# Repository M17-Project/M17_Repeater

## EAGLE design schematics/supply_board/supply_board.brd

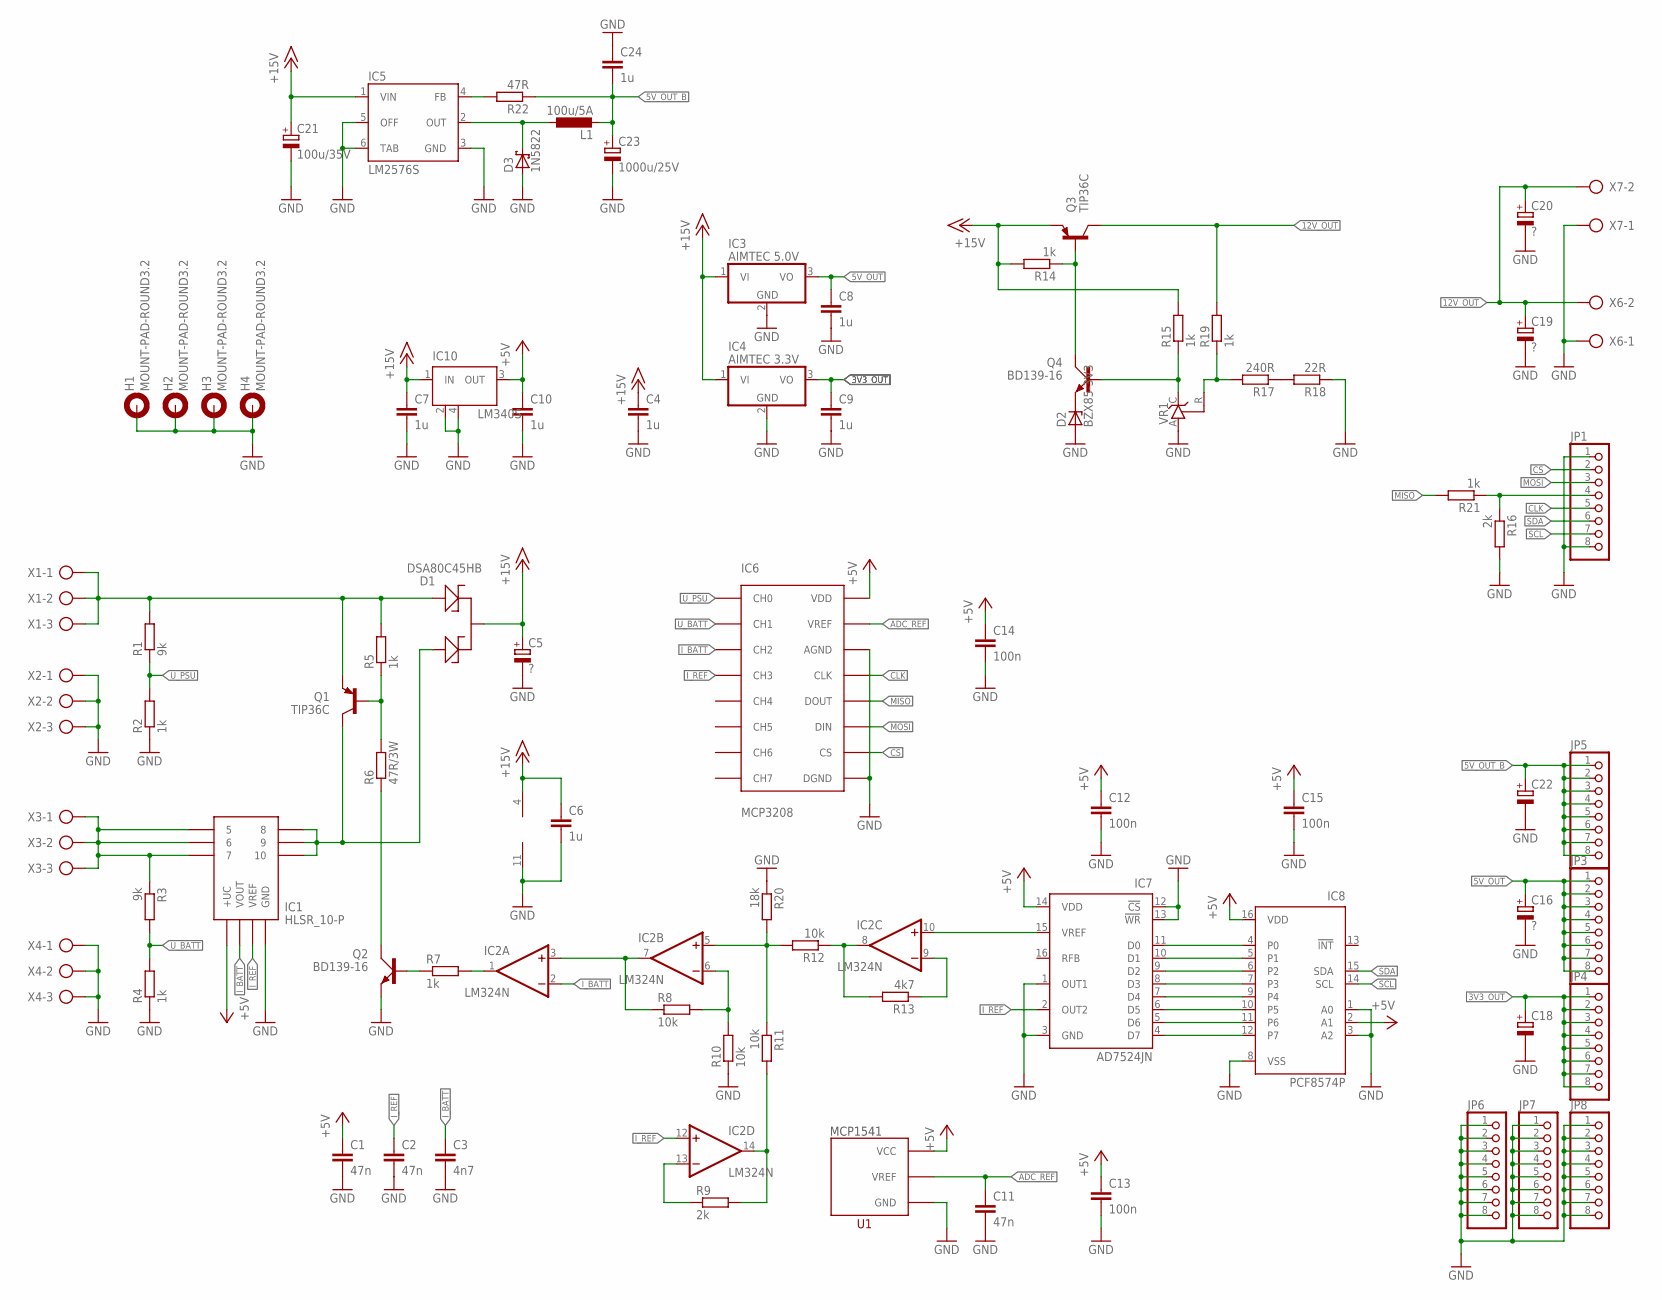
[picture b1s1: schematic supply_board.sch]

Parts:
C1, C2, C11: 47n; C0805
C3: 4n7; C0805
C4, C6, C7, C8, C9, C10, C24: 1u; C0805
C5, C19, C20: ?; E5-13
C12, C13, C14, C15: 100n; C0805
C16: ?; E2,5-6
C18, C22: CPOL-EUE2.5-6; E2,5-6
C21: 100u/35V; E5-10,5
C23: 1000u/25V; E5-10,5
D1: DSA80C45HB; TO247BV
D2: BZX85-3V3; DO41Z10
D3: 1N5822; C4111-15
H1, H2, H3, H4: MOUNT-PAD-ROUND3.2; 3,2-PAD
IC1: HLSR_10-P; HLSR16-P
IC2: LM324N; DIL14
IC3: AIMTEC 5.0V; TO220V
IC4: AIMTEC 3.3V; TO220V
IC5: LM2576S; TO263-5
IC6: MCP3208; DIL16
IC7: AD7524JN; DIL16
IC8: PCF8574P; DIL16
IC10: LM340S; SOT223
JP1, JP3, JP4, JP5, JP6, JP7, JP8: PINHD-1X8; 1X08
L1: 100u/5A; TJ5-U2
Q1, Q3: TIP36C; TO247-V
Q2, Q4: BD139-16; TO126AV
R1, R3: 9k; R0805
R2, R4, R5, R7, R14, R15, R19, R21: 1k; R0805
R6: 47R/3W; 0617/22
R8, R10, R11, R12: 10k; R0805
R9, R16: 2k; R0805
R13: 4k7; R0805
R17: 240R; R0805
R18: 22R; R0805
R20: 18k; R0805
R22: 47R; R0805
U1: VOLT_REFERENCE; SOT23
VR1: TL431CLP; TO92-CLP
X1, X2, X3, X4: AK500/3
X6, X7: AK500/2

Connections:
3V3_OUT: C9.1, C18.+, IC4.3 (VO), JP4.1, JP4.2, JP4.3, JP4.4, JP4.5, JP4.6, JP4.7, JP4.8
5V_OUT: C8.1, C16.+, IC3.3 (VO), JP3.1, JP3.2, JP3.3, JP3.4, JP3.5, JP3.6, JP3.7, JP3.8
5V_OUT_B: C22.+, C23.+, C24.2, JP5.1, JP5.2, JP5.3, JP5.4, JP5.5, JP5.6, JP5.7, JP5.8, L1.2, R22.1
12V_OUT: C19.+, C20.+, Q3.2 (C), R19.2, X6.2, X7.2
+5V: C1.1, C10.1, C12.1, C13.1, C14.1, C15.1, IC1.4 (+UC), IC6.VDD, IC7.14 (VDD), IC8.2 (A1), IC8.16 (VDD), IC10.3 (OUT), U1.1 (VCC)
+15V: C4.1, C5.+, C6.1, C7.1, C21.+, D1.2, IC2.4 (V+), IC3.1 (VI), IC4.1 (VI), IC5.1 (VIN), IC10.1 (IN), Q3.3 (E), R14.2, R15.2
ADC_REF: C11.1, IC6.VREF, U1.2 (VREF)
CLK: IC6.CLK, JP1.5
CS: IC6.CS, JP1.2
GND: C1.2, C2.2, C3.2, C4.2, C5.-, C6.2, C7.2, C8.2, C9.2, C10.2, C11.2, C12.2, C13.2, C14.2, C15.2, C16.-, C18.-, C19.-, C20.-, C21.-, C22.-, C23.-, C24.1, D2.A, D3.A, H1.B3,2, H2.B3,2, H3.B3,2, H4.B3,2, IC1.3 (GND), IC2.11 (V-), IC3.2 (GND), IC4.2 (GND), IC5.3 (GND), IC5.5 (OFF), IC5.6 (TAB), IC6.AGND, IC6.DGND, IC7.1 (OUT1), IC7.3 (GND), IC7.12 (!CS), IC7.13 (!WR), IC8.1 (A0), IC8.3 (A2), IC8.8 (VSS), IC10.2 (GND), IC10.4 (GND), JP1.1, JP1.8, JP6.1, JP6.2, JP6.3, JP6.4, JP6.5, JP6.6, JP6.7, JP6.8, JP7.1, JP7.2, JP7.3, JP7.4, JP7.5, JP7.6, JP7.7, JP7.8, JP8.1, JP8.2, JP8.3, JP8.4, JP8.5, JP8.6, JP8.7, JP8.8, Q2.E, R2.1, R4.1, R10.1, R16.2, R18.1, R20.1, U1.3 (GND), VR1.A, X2.1, X2.2, X2.3, X4.1, X4.2, X4.3, X6.1, X7.1
I_BATT: C3.1, IC1.2 (VOUT), IC2.2 (-IN), IC6.CH2
I_REF: C2.1, IC1.1 (VREF), IC2.12 (+IN), IC6.CH3, IC7.2 (OUT2)
MISO: IC6.DOUT, R21.2
MOSI: IC6.DIN, JP1.3
unnamed: IC1.5, IC1.6, IC1.7, R3.1, X3.1, X3.2, X3.3
unnamed: D1.3, IC1.8, IC1.9, IC1.10, Q1.2 (C)
unnamed: Q1.1 (B), R5.1, R6.2
unnamed: Q2.C, R6.1
unnamed: IC2.6 (-IN), R8.2, R10.2
unnamed: D1.1, Q1.3 (E), R1.2, R5.2, X1.1, X1.2, X1.3
unnamed: Q2.B, R7.1
unnamed: IC2.1 (OUT), R7.2
unnamed: IC2.13 (-IN), R9.1
unnamed: IC2.3 (+IN), IC2.7 (OUT), R8.1
unnamed: IC2.14 (OUT), R9.2, R11.2
unnamed: IC2.5 (+IN), R11.1, R12.2, R20.2
unnamed: IC2.8 (OUT), R12.1, R13.2
unnamed: IC7.11 (D0), IC8.4 (P0)
unnamed: IC7.10 (D1), IC8.5 (P1)
unnamed: IC7.9 (D2), IC8.6 (P2)
unnamed: IC7.8 (D3), IC8.7 (P3)
unnamed: Q3.1 (B), Q4.C, R14.1
unnamed: IC7.7 (D4), IC8.9 (P4)
unnamed: IC7.6 (D5), IC8.10 (P5)
unnamed: IC7.5 (D6), IC8.11 (P6)
unnamed: IC7.4 (D7), IC8.12 (P7)
unnamed: Q4.B, R15.1, VR1.C
unnamed: D2.C, Q4.E
unnamed: IC2.9 (-IN), R13.1
unnamed: IC2.10 (+IN), IC7.15 (VREF)
unnamed: JP1.4, R16.1, R21.1
unnamed: R17.1, R18.2
unnamed: IC5.4 (FB), R22.2
unnamed: R17.2, R19.1, VR1.R
unnamed: D3.C, IC5.2 (OUT), L1.1
SCL: IC8.14 (SCL), JP1.7
SDA: IC8.15 (SDA), JP1.6
U_BATT: IC6.CH1, R3.2, R4.2
U_PSU: IC6.CH0, R1.1, R2.2

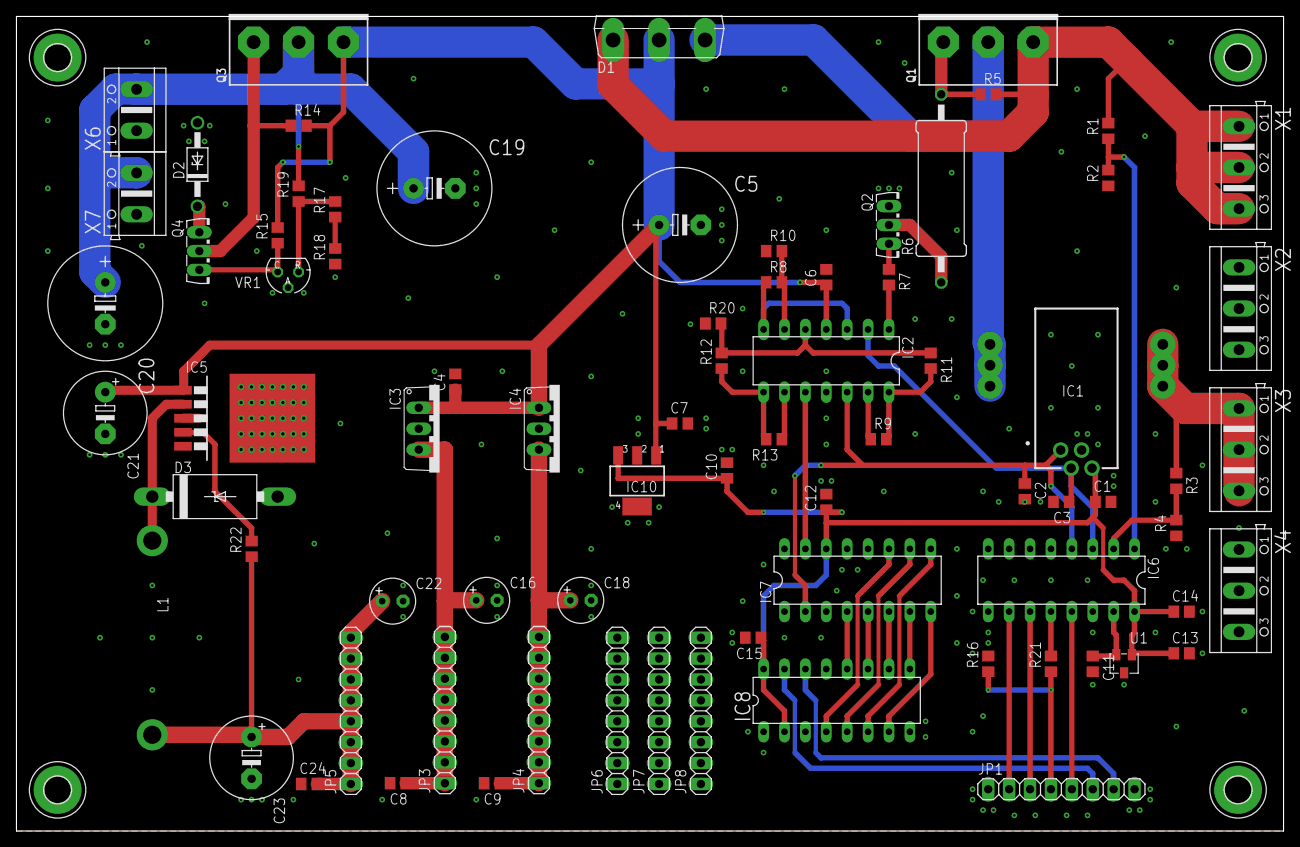
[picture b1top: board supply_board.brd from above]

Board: 2 copper layers, 154.0 x 99.0 mm, 81 parts (0 on the bottom side), 49 nets.

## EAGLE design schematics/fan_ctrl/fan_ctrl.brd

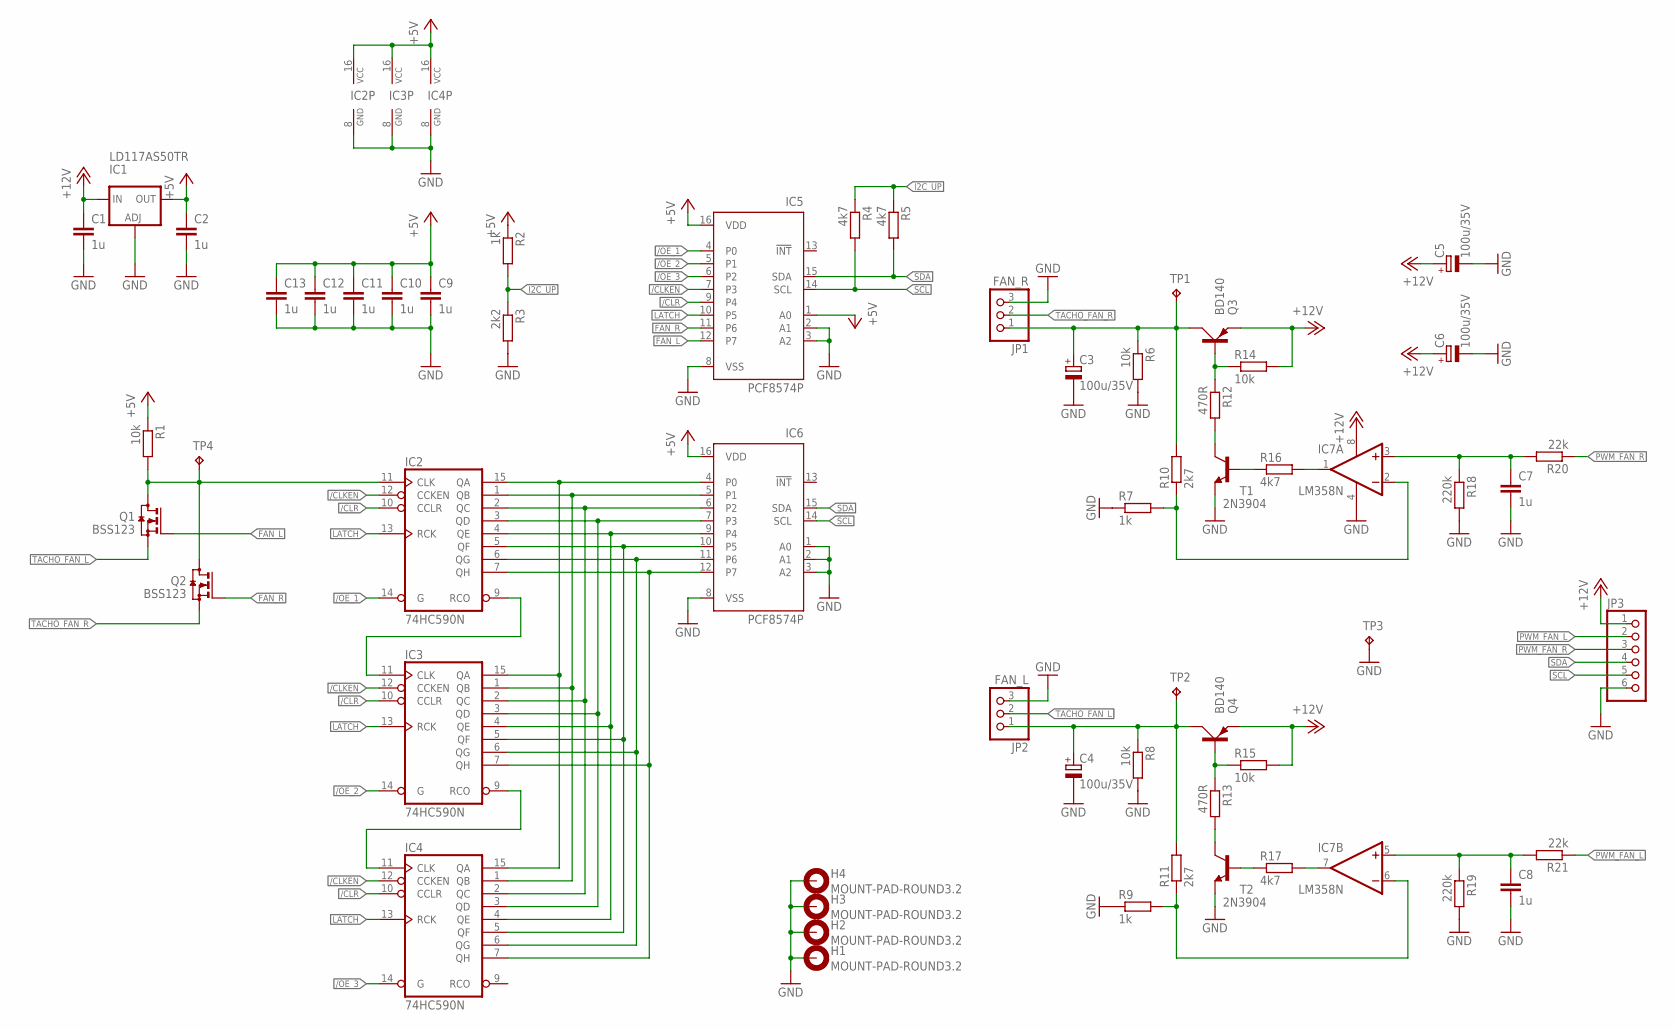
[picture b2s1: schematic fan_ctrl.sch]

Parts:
C1, C2, C7, C8, C9, C10, C11, C12, C13: 1u; C0805
C3, C4, C5, C6: 100u/35V; E3,5-8
H1, H2, H3, H4: MOUNT-PAD-ROUND3.2; 3,2-PAD
IC1: LD117AS50TR; SOT223
IC2, IC3, IC4: 74HC590N; DIL16
IC5, IC6: PCF8574P; DIL16
IC7: LM358N; DIL08
JP1: FAN_R; 1X03
JP2: FAN_L; 1X03
JP3: PINHD-1X6; 1X06
Q1, Q2: BSS123; SOT23
Q3, Q4: BD140; TO126AV
R1, R6, R8, R14, R15: 10k; R0805
R2, R7, R9: 1k; R0805
R3: 2k2; R0805
R4, R5, R16, R17: 4k7; R0805
R10, R11: 2k7; R0805
R12, R13: 470R; R0805
R18, R19: 220k; R0805
R20, R21: 22k; R0805
T1, T2: 2N3904; TO92-EBC
TP1, TP2, TP3, TP4: TPB2,54; B2,54

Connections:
+5V: C2.1, C9.1, C10.1, C11.1, C12.1, C13.1, IC1.4 (OUT), IC2.16 (VCC), IC3.16 (VCC), IC4.16 (VCC), IC5.1 (A0), IC5.16 (VDD), IC6.16 (VDD), R1.1, R2.1
+12V: C1.1, C5.+, C6.+, IC1.3 (IN), IC7.8 (V+), JP3.1, Q3.E, Q4.E, R14.2, R15.2
/CLKEN: IC2.12 (CCKEN), IC3.12 (CCKEN), IC4.12 (CCKEN), IC5.7 (P3)
/CLR: IC2.10 (CCLR), IC3.10 (CCLR), IC4.10 (CCLR), IC5.9 (P4)
/OE_1: IC2.14 (G), IC5.4 (P0)
/OE_2: IC3.14 (G), IC5.5 (P1)
/OE_3: IC4.14 (G), IC5.6 (P2)
FAN_L: IC5.12 (P7), Q1.1 (G)
FAN_R: IC5.11 (P6), Q2.1 (G)
GND: C1.2, C2.2, C3.-, C4.-, C5.-, C6.-, C7.2, C8.2, C9.2, C10.2, C11.2, C12.2, C13.2, H1.B3,2, H2.B3,2, H3.B3,2, H4.B3,2, IC1.1 (ADJ), IC2.8 (GND), IC3.8 (GND), IC4.8 (GND), IC5.2 (A1), IC5.3 (A2), IC5.8 (VSS), IC6.1 (A0), IC6.2 (A1), IC6.3 (A2), IC6.8 (VSS), IC7.4 (V-), JP1.3, JP2.3, JP3.6, R3.2, R6.2, R7.1, R8.2, R9.1, R18.2, R19.2, T1.E, T2.E, TP3.TP
I2C_UP: R2.2, R3.1, R4.1, R5.1
LATCH: IC2.13 (RCK), IC3.13 (RCK), IC4.13 (RCK), IC5.10 (P5)
unnamed: IC2.15 (QA), IC3.15 (QA), IC4.15 (QA), IC6.4 (P0)
unnamed: IC2.1 (QB), IC3.1 (QB), IC4.1 (QB), IC6.5 (P1)
unnamed: IC2.2 (QC), IC3.2 (QC), IC4.2 (QC), IC6.6 (P2)
unnamed: IC2.3 (QD), IC3.3 (QD), IC4.3 (QD), IC6.7 (P3)
unnamed: IC2.4 (QE), IC3.4 (QE), IC4.4 (QE), IC6.9 (P4)
unnamed: IC2.11 (CLK), Q1.3 (D), Q2.3 (D), R1.2, TP4.TP
unnamed: IC2.6 (QG), IC3.6 (QG), IC4.6 (QG), IC6.11 (P6)
unnamed: C7.1, IC7.3 (+IN), R18.1, R20.2
unnamed: R12.2, T1.C
unnamed: C8.1, IC7.5 (+IN), R19.1, R21.2
unnamed: Q3.B, R12.1, R14.1
unnamed: IC3.9 (RCO), IC4.11 (CLK)
unnamed: R13.2, T2.C
unnamed: C3.+, JP1.1, Q3.C, R6.1, R10.2, TP1.TP
unnamed: IC7.6 (-IN), R9.2, R11.1
unnamed: Q4.B, R13.1, R15.1
unnamed: R16.1, T1.B
unnamed: C4.+, JP2.1, Q4.C, R8.1, R11.2, TP2.TP
unnamed: IC7.2 (-IN), R7.2, R10.1
unnamed: IC7.1 (OUT), R16.2
unnamed: R17.1, T2.B
unnamed: IC7.7 (OUT), R17.2
unnamed: IC2.9 (RCO), IC3.11 (CLK)
unnamed: IC2.5 (QF), IC3.5 (QF), IC4.5 (QF), IC6.10 (P5)
unnamed: IC2.7 (QH), IC3.7 (QH), IC4.7 (QH), IC6.12 (P7)
PWM_FAN_L: JP3.2, R21.1
PWM_FAN_R: JP3.3, R20.1
SCL: IC5.14 (SCL), IC6.14 (SCL), JP3.5, R4.2
SDA: IC5.15 (SDA), IC6.15 (SDA), JP3.4, R5.2
TACHO_FAN_L: JP2.2, Q1.2 (S)
TACHO_FAN_R: JP1.2, Q2.2 (S)

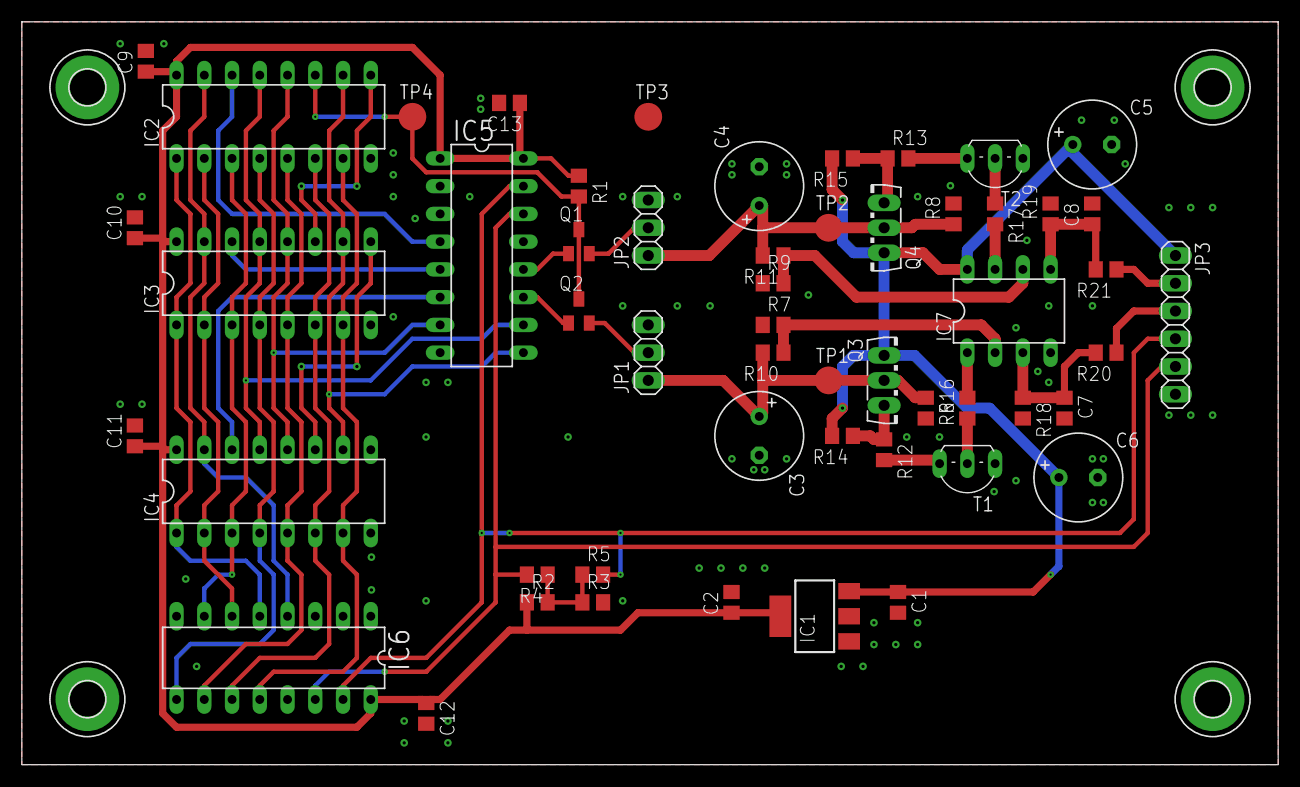
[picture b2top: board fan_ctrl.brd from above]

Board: 2 copper layers, 115.0 x 68.0 mm, 58 parts (0 on the bottom side), 43 nets.

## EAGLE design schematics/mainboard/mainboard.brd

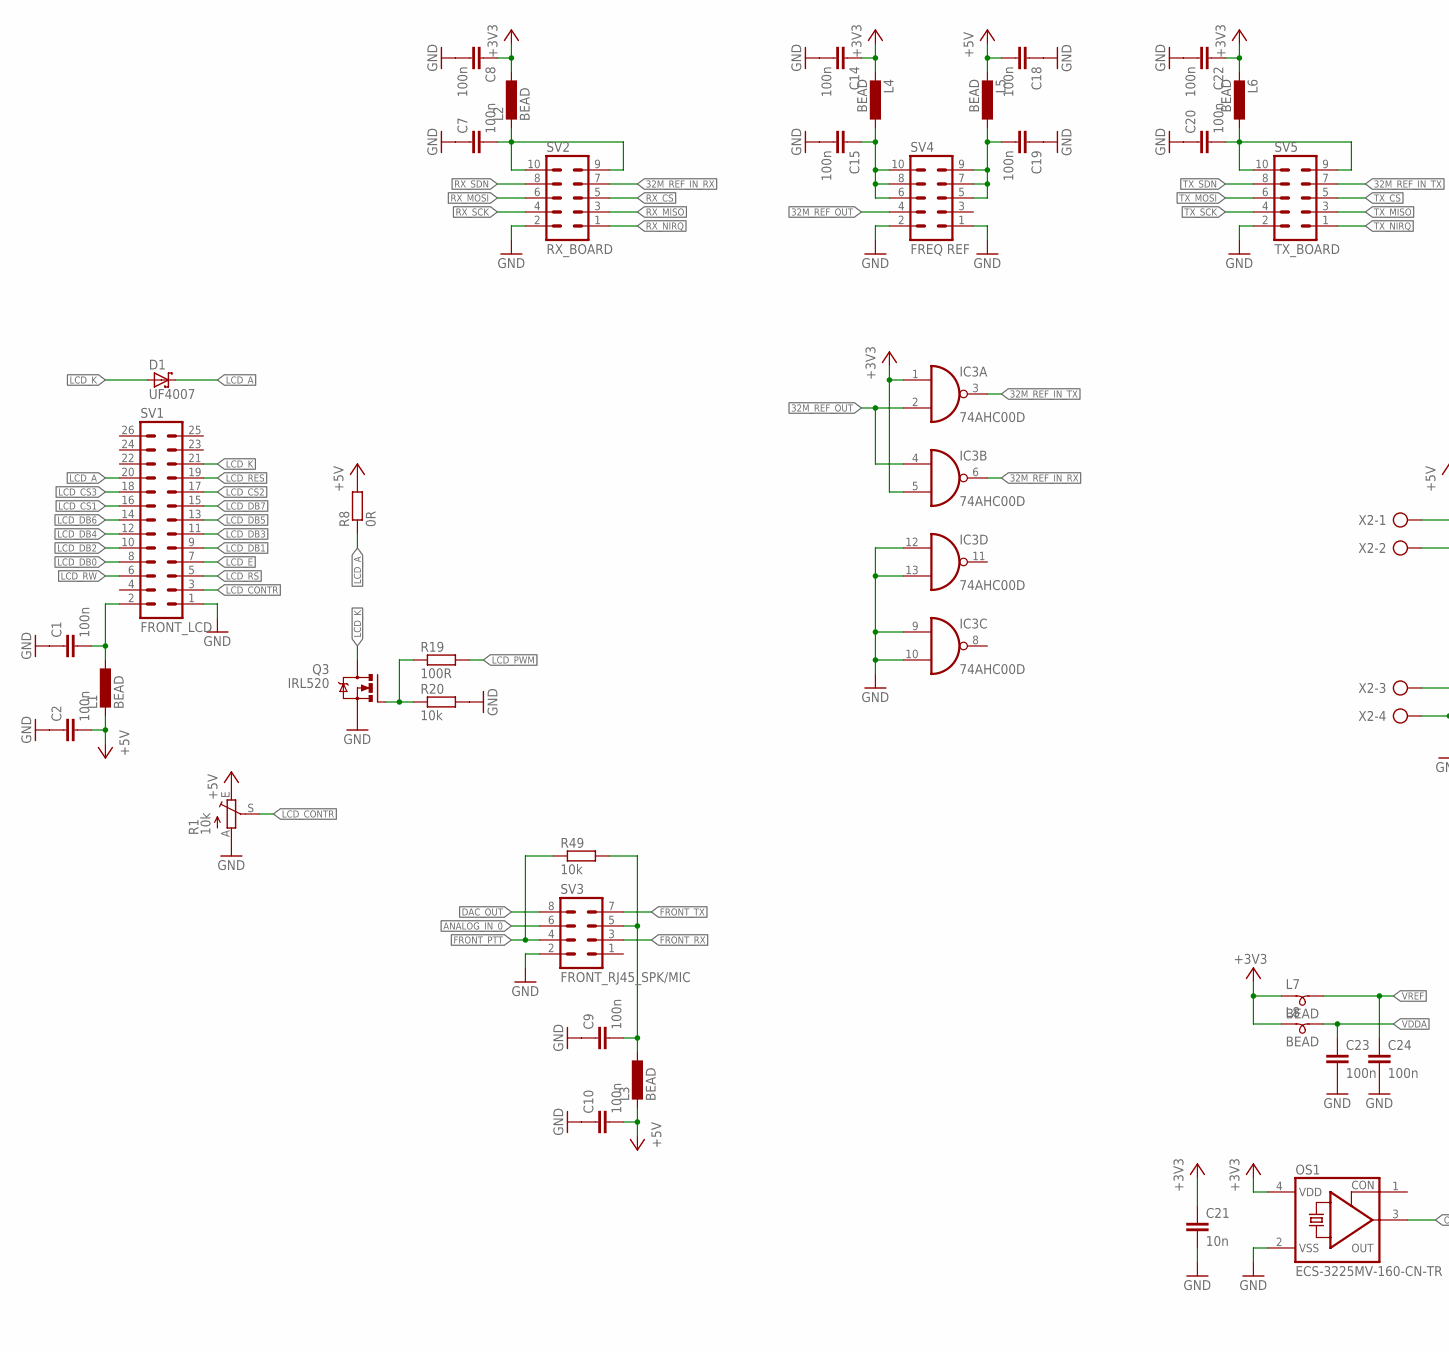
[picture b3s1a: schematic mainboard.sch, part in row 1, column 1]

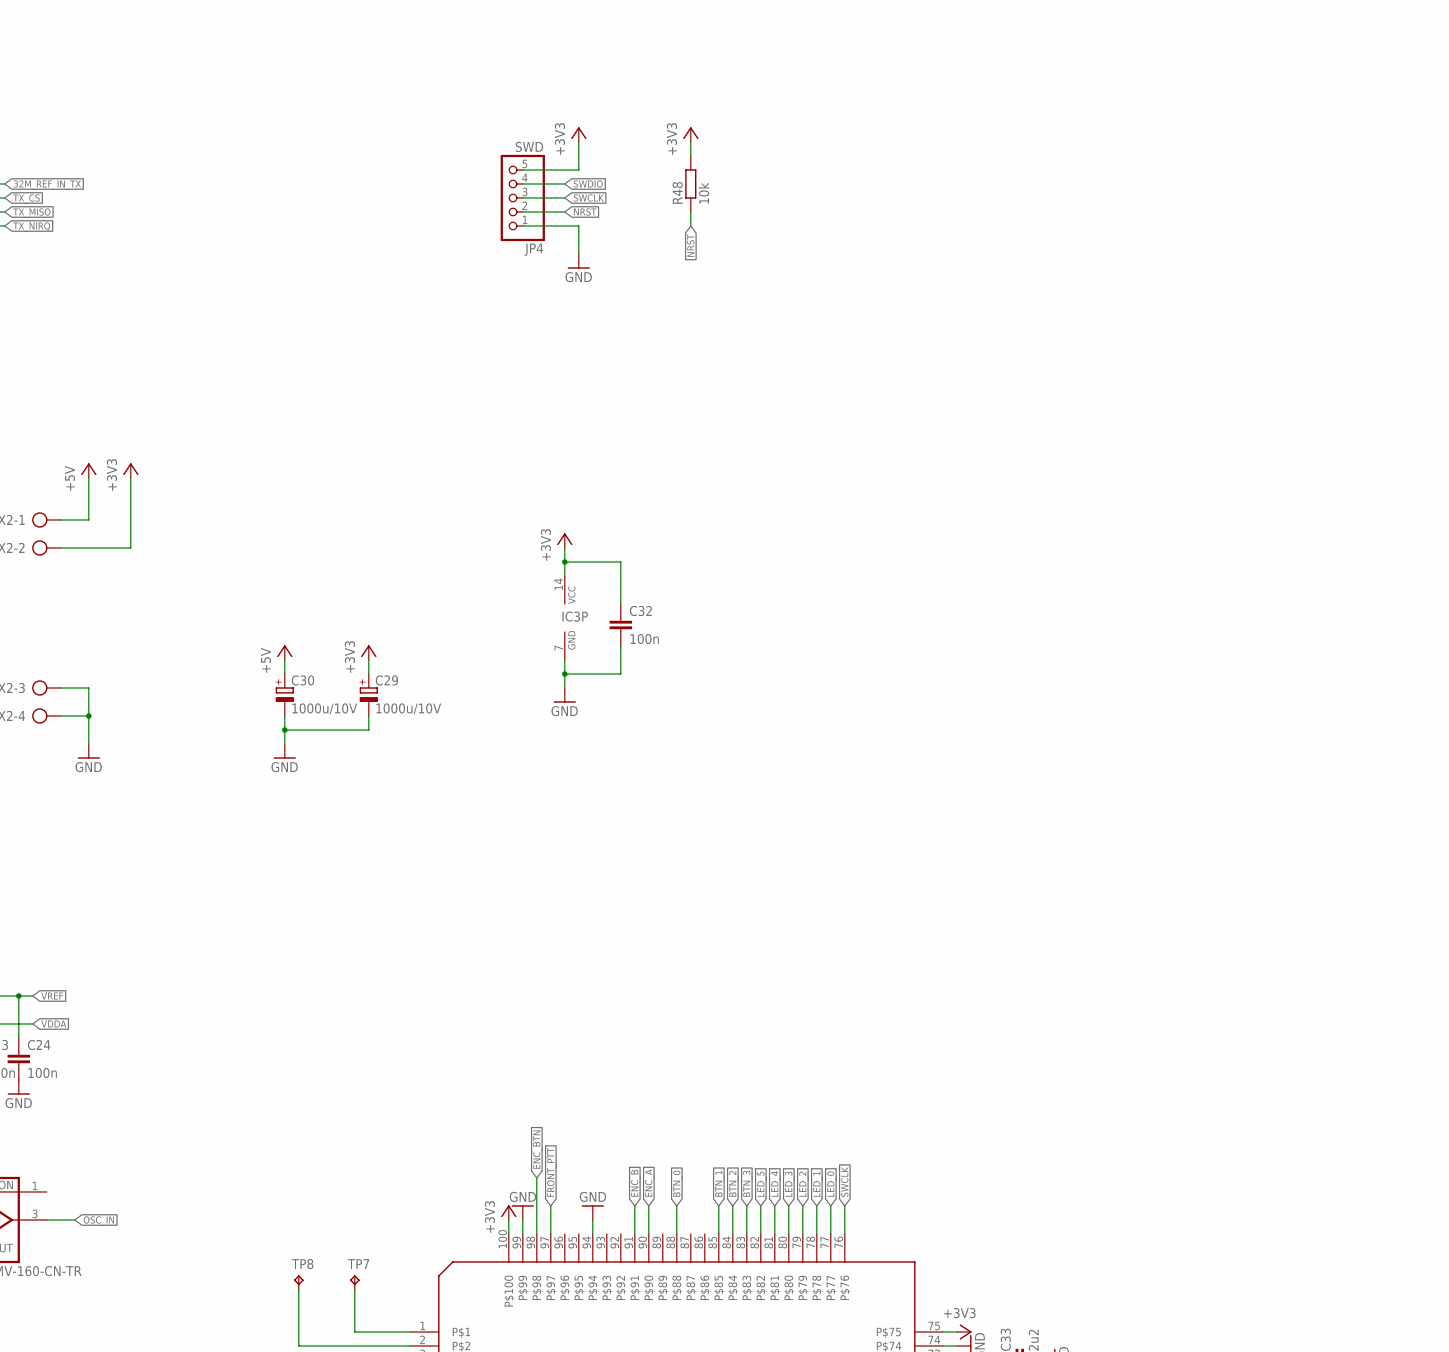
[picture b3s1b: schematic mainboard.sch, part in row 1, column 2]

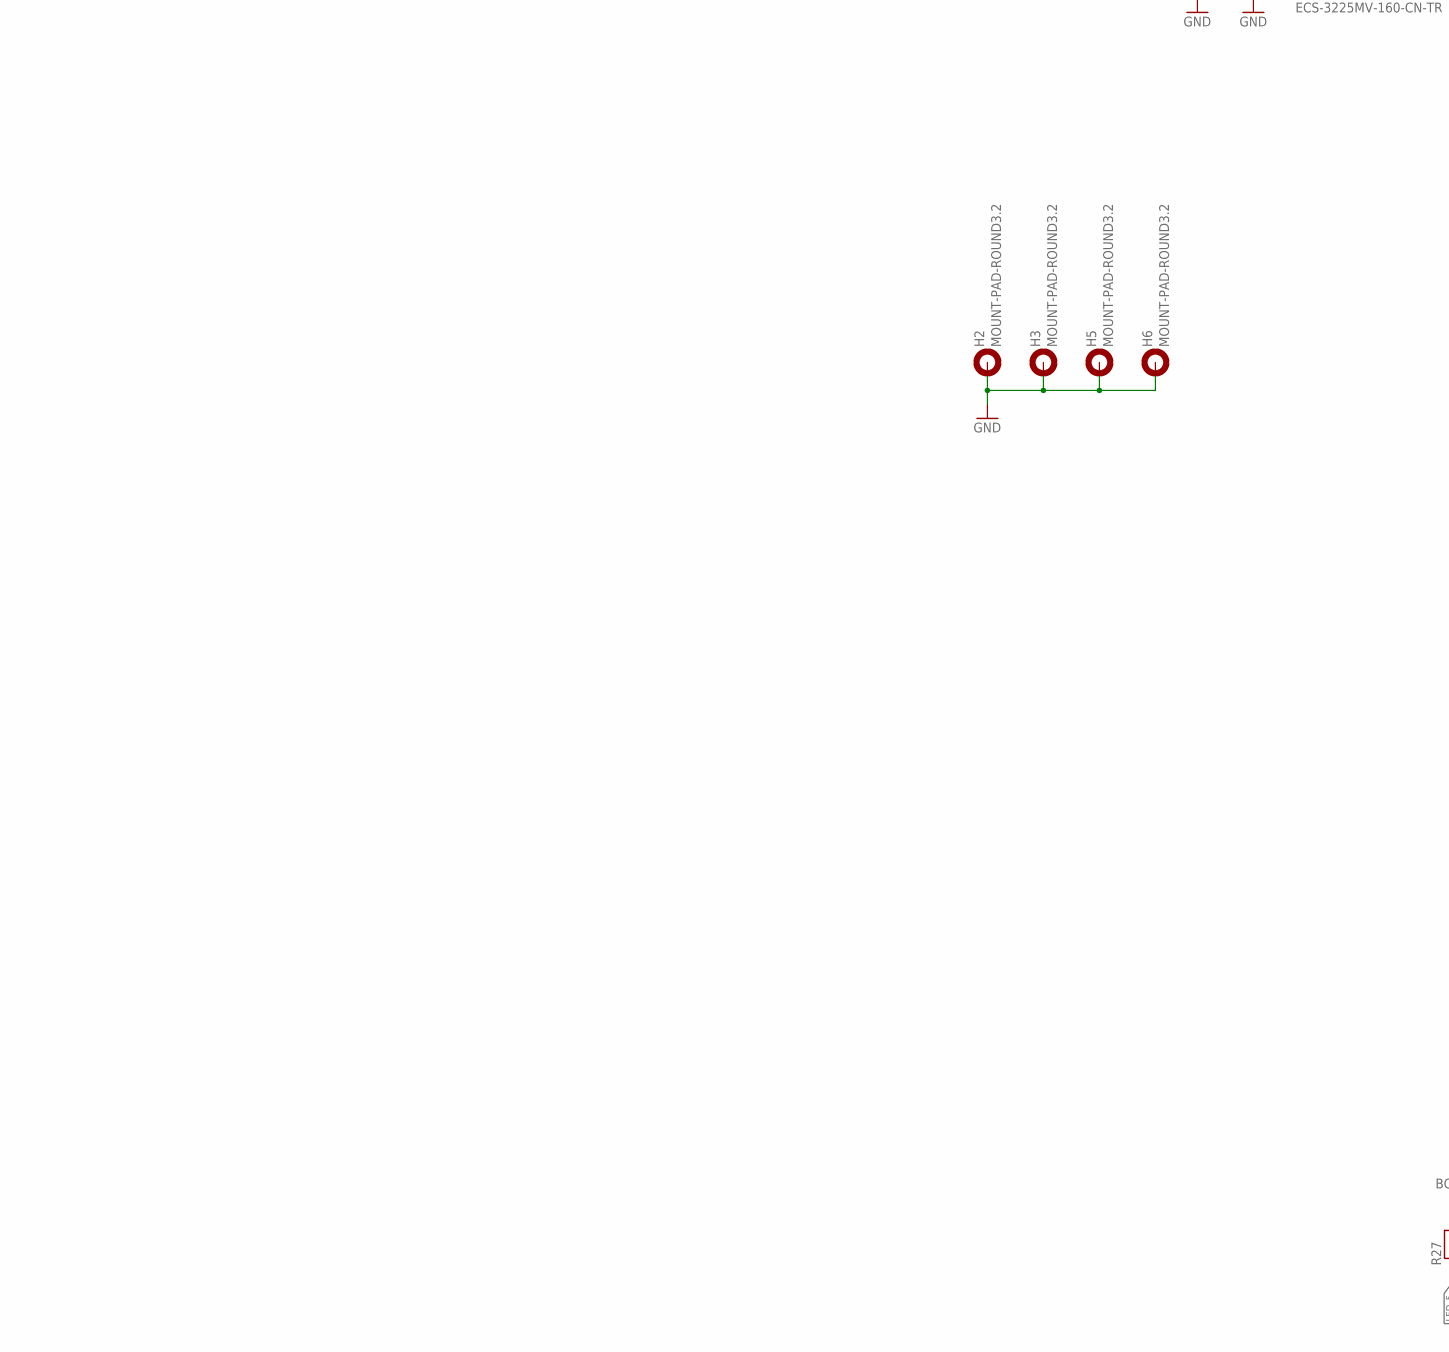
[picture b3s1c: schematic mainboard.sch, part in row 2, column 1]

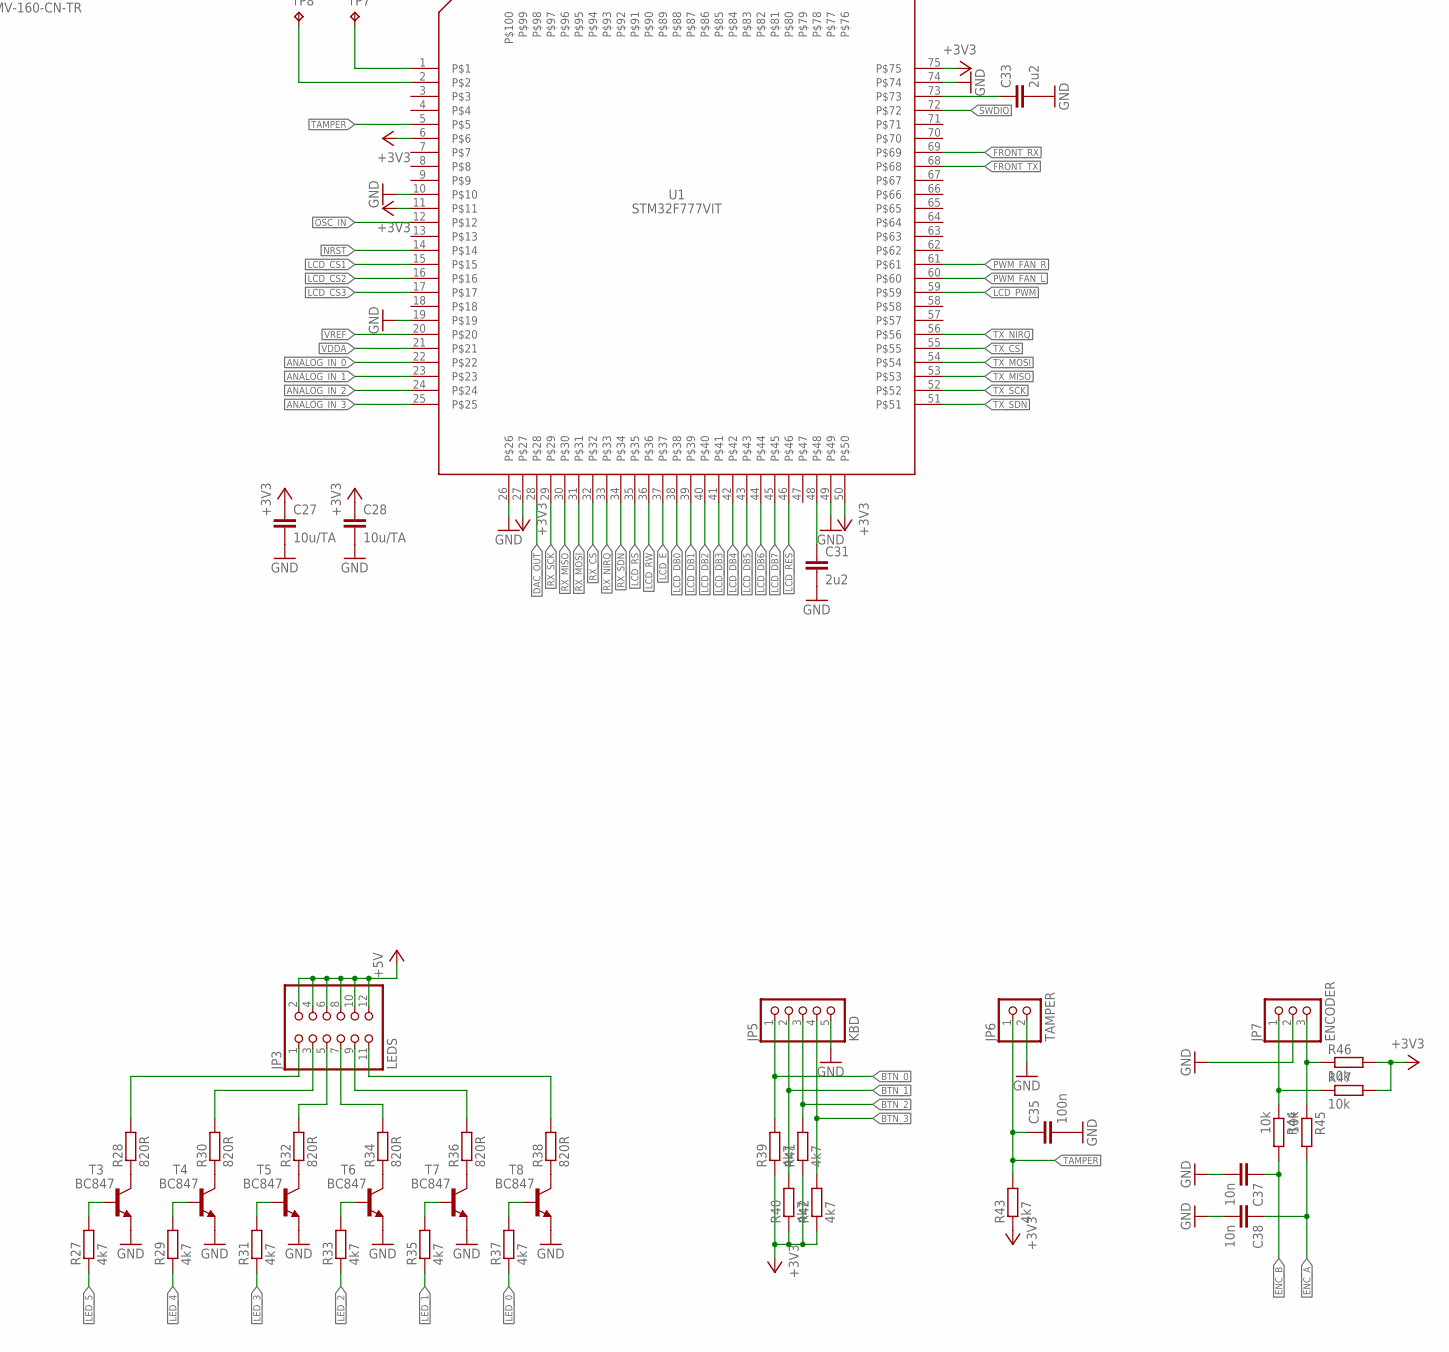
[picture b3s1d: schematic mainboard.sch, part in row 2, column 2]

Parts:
C1, C2, C7, C8, C9, C10, C14, C15, C18, C19, C20, C22, C23, C24, C32, C35: 100n; C0805
C21, C37, C38: 10n; C0805
C27, C28: 10u/TA; C1206
C29, C30: 1000u/10V; E3,5-8
C31, C33: 2u2; C0805
D1: UF4007; DO41-7.6
H2, H3, H5, H6: MOUNT-PAD-ROUND3.2; 3,2-PAD
IC3: 74AHC00D; SO14
JP3: LEDS; 2X06
JP4: SWD; 1X05
JP5: KBD; 1X05
JP6: TAMPER; 1X02
JP7: ENCODER; 1X03
L1, L2, L3, L4, L5, L6: BEAD; 0204/7
L7, L8: BEAD; SM-B5
OS1: ECS-3225MV-160-CN-TR; 3.4X2.7-4-PAD
Q3: IRL520; TO220BV
R1: 10k; CA6V
R8: 0R; R1206
R19: 100R; R0805
R20, R44, R45, R46, R47, R48, R49: 10k; R0805
R27, R29, R31, R33, R35, R37, R39, R40, R41, R42, R43: 4k7; R0805
R28, R30, R32, R34, R36, R38: 820R; R0805
SV1: FRONT_LCD; ML26
SV2: RX_BOARD; ML10
SV3: FRONT_RJ45_SPK/MIC; MA04-2
SV4: FREQ REF; ML10
SV5: TX_BOARD; ML10
T3, T4, T5, T6, T7, T8: BC847; SOT23
TP7, TP8: TPB2,54; B2,54
U1: STM32F777VIT; LQFP100
X2: AK500/4

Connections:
32M_REF_IN_RX: IC3.6 (O), SV2.7
32M_REF_IN_TX: IC3.3 (O), SV5.7
32M_REF_OUT: IC3.2 (I1), IC3.4 (I0), SV4.4
+3V3: C8.1, C14.1, C21.1, C22.1, C27.1, C28.1, C29.+, C32.1, IC3.1 (I0), IC3.5 (I1), IC3.14 (VCC), JP4.5, L2.1, L4.2, L6.2, L7.1, L8.1, OS1.4 (VDD), R39.1, R40.1, R41.1, R42.1, R43.1, R46.2, R47.2, R48.2, U1.6, U1.11, U1.27, U1.50, U1.75, U1.100, X2.2
+5V: C2.2, C10.2, C18.2, C30.+, JP3.2, JP3.4, JP3.6, JP3.8, JP3.10, JP3.12, L1.2, L3.2, L5.2, R1.E, R8.2, X2.1
ANALOG_IN_0: SV3.6, U1.22
ANALOG_IN_1: U1.23
ANALOG_IN_2: U1.24
ANALOG_IN_3: U1.25
BTN_0: JP5.1, R39.2, U1.88
BTN_1: JP5.2, R40.2, U1.85
BTN_2: JP5.3, R41.2, U1.84
BTN_3: JP5.4, R42.2, U1.83
DAC_OUT: SV3.8, U1.28
ENC_A: C38.1, R45.2, U1.90
ENC_B: C37.1, R44.2, U1.91
ENC_BTN: U1.98
FRONT_PTT: R49.1, SV3.4, U1.97
FRONT_RX: SV3.3, U1.69
FRONT_TX: SV3.7, U1.68
GND: C1.1, C2.1, C7.1, C8.2, C9.1, C10.1, C14.2, C15.2, C18.1, C19.1, C20.1, C21.2, C22.2, C23.2, C24.2, C27.2, C28.2, C29.-, C30.-, C31.2, C32.2, C33.2, C35.2, C37.2, C38.2, H2.B3,2, H3.B3,2, H5.B3,2, H6.B3,2, IC3.7 (GND), IC3.9 (I0), IC3.10 (I1), IC3.12 (I0), IC3.13 (I1), JP4.1, JP5.5, JP6.2, JP7.2, OS1.2 (VSS), Q3.S, R1.A, R20.2, SV1.1, SV2.2, SV3.2, SV4.1, SV4.2, SV5.2, T3.2 (E), T4.2 (E), T5.2 (E), T6.2 (E), T7.2 (E), T8.2 (E), U1.10, U1.19, U1.26, U1.49, U1.74, U1.94, U1.99, X2.3, X2.4
LCD_A: D1.C, R8.1, SV1.20
LCD_CONTR: R1.S, SV1.3
LCD_CS1: SV1.16, U1.15
LCD_CS2: SV1.17, U1.16
LCD_CS3: SV1.18, U1.17
LCD_DB0: SV1.8, U1.38
LCD_DB1: SV1.9, U1.39
LCD_DB2: SV1.10, U1.40
LCD_DB3: SV1.11, U1.41
LCD_DB4: SV1.12, U1.42
LCD_DB5: SV1.13, U1.43
LCD_DB6: SV1.14, U1.44
LCD_DB7: SV1.15, U1.45
LCD_E: SV1.7, U1.37
LCD_K: D1.A, Q3.D, SV1.21
LCD_PWM: R19.2, U1.59
LCD_RES: SV1.19, U1.46
LCD_RS: SV1.5, U1.35
LCD_RW: SV1.6, U1.36
LED_0: R37.1, U1.77
LED_1: R35.1, U1.78
LED_2: R33.1, U1.79
LED_3: R31.1, U1.80
LED_4: R29.1, U1.81
LED_5: R27.1, U1.82
unnamed: Q3.G, R19.1, R20.1
unnamed: C15.1, L4.1, SV4.6, SV4.8, SV4.10
unnamed: C19.2, L5.1, SV4.5, SV4.7, SV4.9
unnamed: C20.2, L6.1, SV5.9, SV5.10
unnamed: C1.2, L1.1, SV1.2
unnamed: C7.2, L2.2, SV2.9, SV2.10
unnamed: C9.2, L3.1, R49.2, SV3.5
unnamed: C31.1, U1.48
unnamed: C33.1, U1.73
unnamed: R27.2, T3.1 (B)
unnamed: R28.1, T3.3 (C)
unnamed: JP3.1, R28.2
unnamed: JP3.3, R30.2
unnamed: R29.2, T4.1 (B)
unnamed: R30.1, T4.3 (C)
unnamed: JP3.5, R32.2
unnamed: R31.2, T5.1 (B)
unnamed: R32.1, T5.3 (C)
unnamed: JP3.7, R34.2
unnamed: R33.2, T6.1 (B)
unnamed: R34.1, T6.3 (C)
unnamed: JP3.9, R36.2
unnamed: R35.2, T7.1 (B)
unnamed: R36.1, T7.3 (C)
unnamed: JP3.11, R38.2
unnamed: R37.2, T8.1 (B)
unnamed: R38.1, T8.3 (C)
unnamed: TP7.TP, U1.1
unnamed: JP7.3, R45.1, R46.1
unnamed: JP7.1, R44.1, R47.1
unnamed: TP8.TP, U1.2
NRST: JP4.2, R48.1, U1.14
OSC_IN: OS1.3 (OUT), U1.12
PWM_FAN_L: U1.60
PWM_FAN_R: U1.61
RX_CS: SV2.5, U1.32
RX_MISO: SV2.3, U1.30
RX_MOSI: SV2.6, U1.31
RX_NIRQ: SV2.1, U1.33
RX_SCK: SV2.4, U1.29
RX_SDN: SV2.8, U1.34
SWCLK: JP4.3, U1.76
SWDIO: JP4.4, U1.72
TAMPER: C35.1, JP6.1, R43.2, U1.5
TX_CS: SV5.5, U1.55
TX_MISO: SV5.3, U1.53
TX_MOSI: SV5.6, U1.54
TX_NIRQ: SV5.1, U1.56
TX_SCK: SV5.4, U1.52
TX_SDN: SV5.8, U1.51
VDDA: C23.1, L8.2, U1.21
VREF: C24.1, L7.2, U1.20

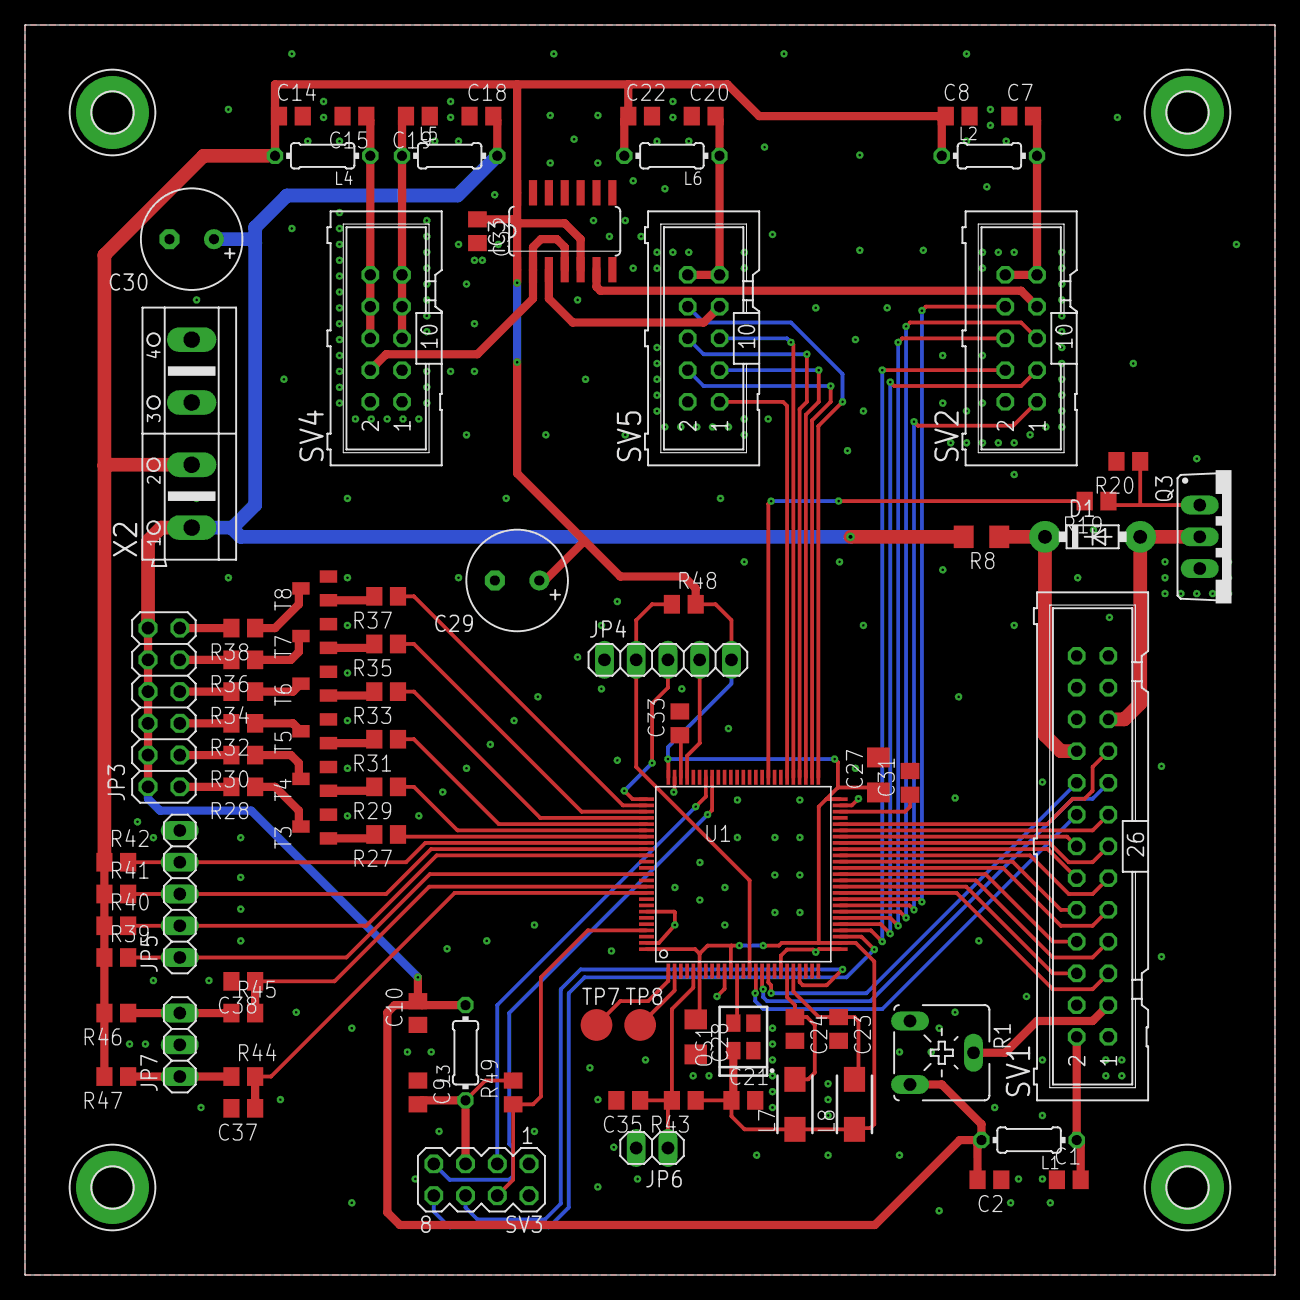
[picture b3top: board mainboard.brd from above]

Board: 2 copper layers, 100.0 x 100.0 mm, 88 parts (0 on the bottom side), 92 nets.
